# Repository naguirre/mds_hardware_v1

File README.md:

# mds-hardware

KiCad sources and fabrication outputs for a small network audio player board built around an Allwinner F1C200s SoC, an ESP32-C3 for Wi-Fi, NAND flash storage, an EA3036 power management IC, and an audio DAC daughter board.

The repository contains two KiCad projects:
- [network_player/](network_player/) — the main board
- [dac/](dac/) — the audio DAC daughter board

## Versions

| Version | Date       | Status                                         | Schematic | PCB | Gerbers |
|---------|------------|------------------------------------------------|-----------|-----|---------|
| v1      | 2024-01-15 | Sent to JLCPCB, had routing issues             | [PDF](docs/v1/schematic.pdf) | [PDF](docs/v1/pcb.pdf) | [ZIP](docs/v1/gerbers.zip) |
| v1.1    | 2024-06-02 | Sent to JLCPCB, fixes routing issues of v1     | [PDF](docs/v1.1/schematic.pdf) | [PDF](docs/v1.1/pcb.pdf) | [ZIP](docs/v1.1/gerbers.zip) |
| v2      | 2024-06-01 | Full redesign, never produced                  | [PDF](docs/v2/schematic.pdf) | [PDF](docs/v2/pcb.pdf) | [ZIP](docs/v2/gerbers.zip) |

Each version lives on its own branch: [`users/nico/v1`](../../tree/users/nico/v1), [`users/nico/v1.1`](../../tree/users/nico/v1.1), [`users/nico/v2`](../../tree/users/nico/v2). The `v1_jlcpcb` tag points to the JLCPCB return files for v1.

## Latest produced version: v1.1

v1.1 is the version that was actually fabricated and assembled by JLCPCB. Compared to v1, it brings the following changes (see commit [b7ff0fe](../../commit/b7ff0fe)):

- Removed the discrete transistors used for ESP32 boot/reset, driven directly from F1C200s GPIOs instead
- EA3036 enable pin tied to 3.3 V
- Added a RST button that pulls the MISO line to ground to disable booting from flash
- ESP32 moved to SPI1; SPI0 is now shared between the NAND flash and the RPi connector

### Schematic

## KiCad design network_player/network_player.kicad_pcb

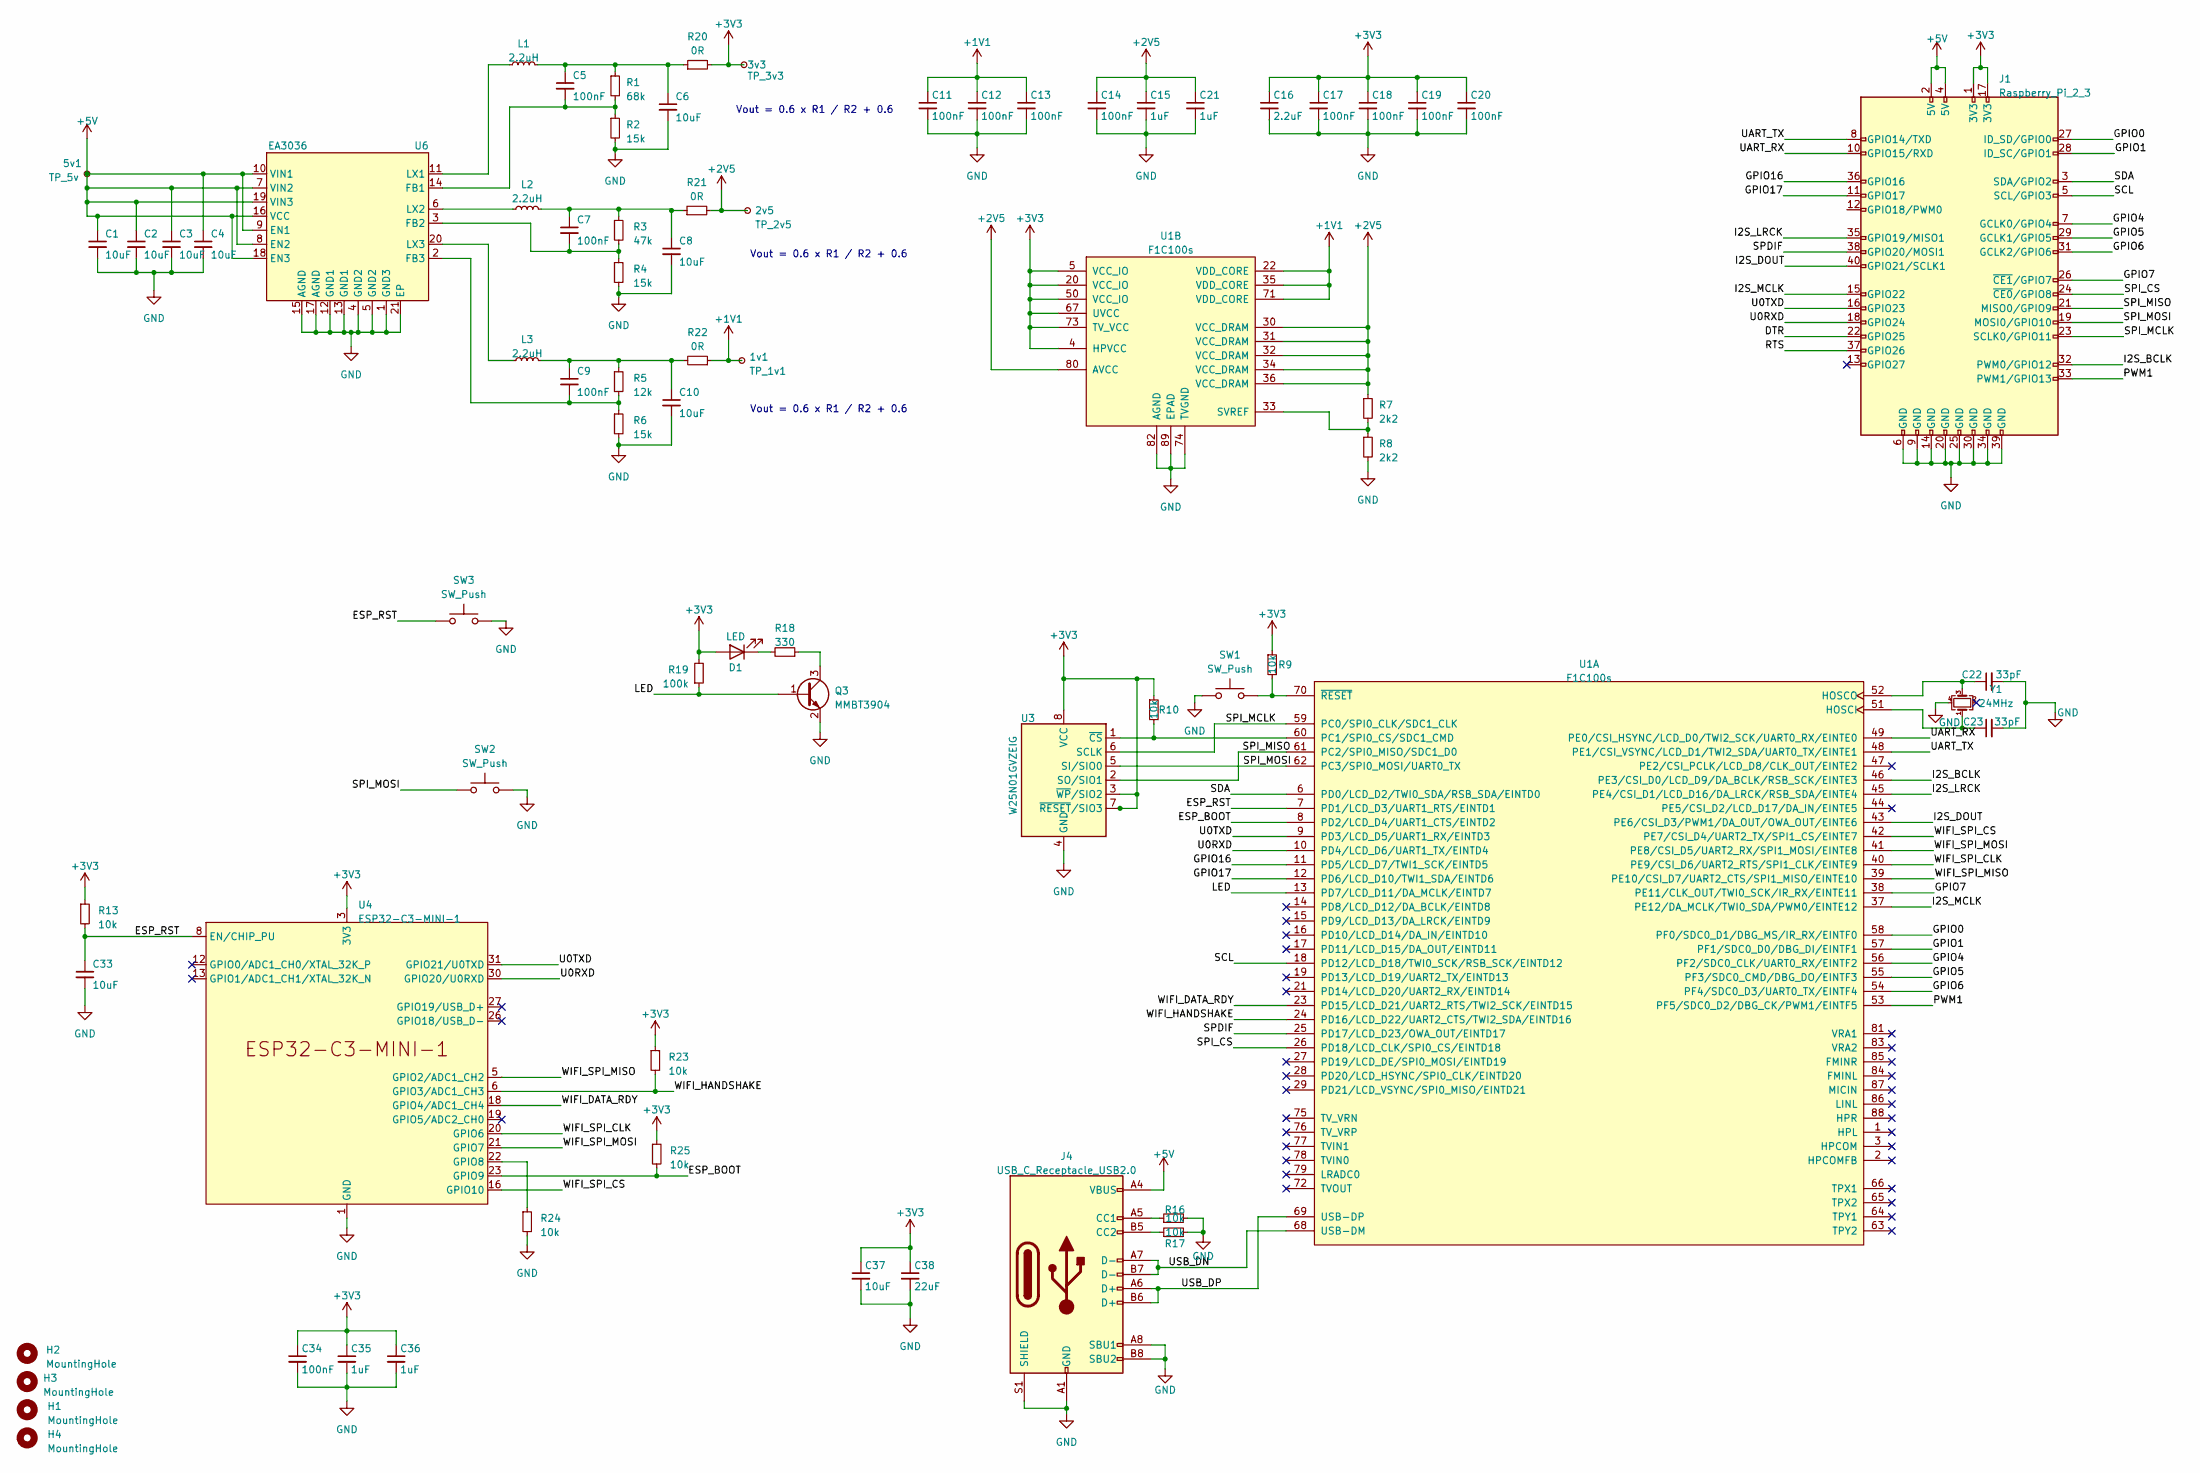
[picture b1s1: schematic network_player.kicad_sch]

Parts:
1v1: TP_1v1; TestPoint_Pad_D1.0mm
2v5: TP_2v5; TestPoint_Pad_D1.0mm
3v3: TP_3v3; TestPoint_Pad_D1.0mm
5v1: TP_5v; TestPoint_Pad_D1.0mm
C1, C2, C3, C4, C6, C8, C10, C33, C37: 10uF; C_0402_1005Metric; LCSC C15525
C5, C7, C9, C11, C12, C13, C14, C17, C18, C19, C20, C34: 100nF; C_0402_1005Metric; LCSC C307331
C15, C21, C35, C36: 1uF; C_0402_1005Metric; LCSC C52923
C16: 2.2uF; C_0402_1005Metric; LCSC C12530
C22, C23: 33pF; C_0402_1005Metric; LCSC C1562
C38: 22uF; C_0805_2012Metric; LCSC C59461
D1: LED; LED_0603_1608Metric; LCSC C2290
H1, H2, H3, H4: MountingHole; MountingHole_2.7mm_M2.5
J1: Raspberry_Pi_2_3; PinHeader_2x20_P2.54mm_Vertical
J4: USB_C_Receptacle_USB2.0; USB_C_Receptacle_GT-USB-7010; LCSC C963370
L1, L2, L3: 2.2uH; L_0805_2012Metric; LCSC C1043
Q3: MMBT3904; SOT-23; LCSC C20526
R1: 68k; R_0402_1005Metric; LCSC C36871
R2, R4, R6: 15k; R_0402_1005Metric; LCSC C25756
R3: 47k; R_0402_1005Metric; LCSC C25792
R5: 12k; R_0402_1005Metric; LCSC C25752
R7, R8: 2k2; R_0402_1005Metric; LCSC C25879
R9, R10, R13, R16, R17, R23, R24, R25: 10k; R_0402_1005Metric; LCSC C25744
R18: 330; R_0402_1005Metric; LCSC C25104
R19: 100k; R_0402_1005Metric; LCSC C25741
R20, R21, R22: 0R; R_0402_1005Metric; LCSC C17168
SW1, SW2, SW3: SW_Push; SW_Push_1P1T_XKB_TS-1187A; LCSC C318884
U1: F1C100s; QFN-88_EP_10x10_Pitch0.4mm; LCSC C2879851
U3: W25N01GVZEIG; WSON-8-1EP_8x6mm_P1.27mm_EP3.4x4.3mm; LCSC C88868
U4: ESP32-C3-MINI-1; LCSC C2838502
U6: EA3036; QFN-20-1EP_3x3mm_P0.4mm_EP1.65x1.65mm; LCSC C570857
Y1: 24MHz; Crystal_SMD_SeikoEpson_TSX3225-4Pin_3.2x2.5mm; LCSC C15643

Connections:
+1V1: 1v1.1, C11.1, C12.1, C13.1, R22.1, U1.22 (VDD_CORE), U1.35 (VDD_CORE), U1.71 (VDD_CORE)
+2V5: 2v5.1, C14.1, C15.1, C21.1, R7.1, R21.2, U1.30 (VCC_DRAM), U1.31 (VCC_DRAM), U1.32 (VCC_DRAM), U1.34 (VCC_DRAM), U1.36 (VCC_DRAM), U1.80 (AVCC)
+3V3: 3v3.1, C16.1, C17.1, C18.1, C19.1, C20.1, C34.1, C35.1, C36.1, C37.1, C38.1, D1.2 (A), J1.1 (3V3), J1.17 (3V3), R9.1, R10.1, R13.1, R19.2, R20.2, R23.1, R25.1, U1.4 (HPVCC), U1.5 (VCC_IO), U1.20 (VCC_IO), U1.50 (VCC_IO), U1.67 (UVCC), U1.73 (TV_VCC), U3.3 (~WP/SIO2), U3.7 (~RESET/SIO3), U3.8 (VCC), U4.3 (3V3)
+5V: 5v1.1, C1.1, C2.1, C3.1, C4.1, J1.2 (5V), J1.4 (5V), J4.A4 (VBUS), J4.A9 (VBUS), J4.B4 (VBUS), J4.B9 (VBUS), U6.7 (VIN2), U6.8 (EN2), U6.9 (EN1), U6.10 (VIN1), U6.16 (VCC), U6.18 (EN3), U6.19 (VIN3)
/DTR: J1.22 (GPIO25)
/ESP_BOOT: R25.2, U1.8 (PD2/LCD_D4/UART1_CTS/EINTD2), U4.23 (GPIO9)
/ESP_RST: C33.1, R13.2, SW3.1, U1.7 (PD1/LCD_D3/UART1_RTS/EINTD1), U4.8 (EN/CHIP_PU)
/GPIO0: J1.27 (ID_SD/GPIO0), U1.58 (PF0/SDC0_D1/DBG_MS/IR_RX/EINTF0)
/GPIO1: J1.28 (ID_SC/GPIO1), U1.57 (PF1/SDC0_D0/DBG_DI/EINTF1)
/GPIO4: J1.7 (GCLK0/GPIO4), U1.56 (PF2/SDC0_CLK/UART0_RX/EINTF2)
/GPIO5: J1.29 (GCLK1/GPIO5), U1.55 (PF3/SDC0_CMD/DBG_DO/EINTF3)
/GPIO6: J1.31 (GCLK2/GPIO6), U1.54 (PF4/SDC0_D3/UART0_TX/EINTF4)
/GPIO7: J1.26 (~CE1/GPIO7), U1.38 (PE11/CLK_OUT/TWI0_SCK/IR_RX/EINTE11)
/GPIO16: J1.36 (GPIO16), U1.11 (PD5/LCD_D7/TWI1_SCK/EINTD5)
/GPIO17: J1.11 (GPIO17), U1.12 (PD6/LCD_D10/TWI1_SDA/EINTD6)
/I2S_BCLK: J1.32 (PWM0/GPIO12), U1.46 (PE3/CSI_D0/LCD_D9/DA_BCLK/RSB_SCK/EINTE3)
/I2S_DOUT: J1.40 (GPIO21/SCLK1), U1.43 (PE6/CSI_D3/PWM1/DA_OUT/OWA_OUT/EINTE6)
/I2S_LRCK: J1.35 (GPIO19/MISO1), U1.45 (PE4/CSI_D1/LCD_D16/DA_LRCK/RSB_SDA/EINT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)
/I2S_MCLK: J1.15 (GPIO22), U1.37 (PE12/DA_MCLK/TWI0_SDA/PWM0/EINTE12)
/LED: Q3.1 (B), R19.1, U1.13 (PD7/LCD_D11/DA_MCLK/EINTD7)
/PWM1: J1.33 (PWM1/GPIO13), U1.53 (PF5/SDC0_D2/DBG_CK/PWM1/EINTF5)
/RTS: J1.37 (GPIO26)
/SCL: J1.5 (SCL/GPIO3), U1.18 (PD12/LCD_D18/TWI0_SCK/RSB_SCK/EINTD12)
/SDA: J1.3 (SDA/GPIO2), U1.6 (PD0/LCD_D2/TWI0_SDA/RSB_SDA/EINTD0)
/SPDIF: J1.38 (GPIO20/MOSI1), U1.25 (PD17/LCD_D23/OWA_OUT/EINTD17)
/SPI_CS: J1.24 (~CE0/GPIO8), U1.26 (PD18/LCD_CLK/SPI0_CS/EINTD18)
/SPI_MCLK: J1.23 (SCLK0/GPIO11), U1.59 (PC0/SPI0_CLK/SDC1_CLK), U3.6 (SCLK)
/SPI_MISO: J1.21 (MISO0/GPIO9), U1.61 (PC2/SPI0_MISO/SDC1_D0), U3.2 (SO/SIO1)
/SPI_MOSI: J1.19 (MOSI0/GPIO10), SW2.1, U1.62 (PC3/SPI0_MOSI/UART0_TX), U3.5 (SI/SIO0)
/U0RXD: J1.18 (GPIO24), U1.10 (PD4/LCD_D6/UART1_TX/EINTD4), U4.30 (GPIO20/U0RXD)
/U0TXD: J1.16 (GPIO23), U1.9 (PD3/LCD_D5/UART1_RX/EINTD3), U4.31 (GPIO21/U0TXD)
/UART_RX: J1.10 (GPIO15/RXD), U1.49 (PE0/CSI_HSYNC/LCD_D0/TWI2_SCK/UART0_RX/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)
/UART_TX: J1.8 (GPIO14/TXD), U1.48 (PE1/CSI_VSYNC/LCD_D1/TWI2_SDA/UART0_TX/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)
/USB_DN: J4.A7 (D-), J4.B7 (D-), U1.68 (USB-DM)
/USB_DP: J4.A6 (D+), J4.B6 (D+), U1.69 (USB-DP)
/WIFI_DATA_RDY: U1.23 (PD15/LCD_D21/UART2_RTS/TWI2_SCK/EINTD15), U4.18 (GPIO4/ADC1_CH4)
/WIFI_HANDSHAKE: R23.2, U1.24 (PD16/LCD_D22/UART2_CTS/TWI2_SDA/EINTD16), U4.6 (GPIO3/ADC1_CH3)
/WIFI_SPI_CLK: U1.40 (PE9/CSI_D6/UART2_RTS/SPI1_CLK/EINTE9), U4.20 (GPIO6)
/WIFI_SPI_CS: U1.42 (PE7/CSI_D4/UART2_TX/SPI1_CS/EINTE7), U4.16 (GPIO10)
/WIFI_SPI_MISO: U1.39 (PE10/CSI_D7/UART2_CTS/SPI1_MISO/EINTE10), U4.5 (GPIO2/ADC1_CH2)
/WIFI_SPI_MOSI: U1.41 (PE8/CSI_D5/UART2_RX/SPI1_MOSI/EINTE8), U4.21 (GPIO7)
GND: C1.2, C2.2, C3.2, C4.2, C6.2, C8.2, C10.2, C11.2, C12.2, C13.2, C14.2, C15.2, C16.2, C17.2, C18.2, C19.2, C20.2, C21.2, C22.2, C23.2, C33.2, C34.2, C35.2, C36.2, C37.2, C38.2, J1.6 (GND), J1.9 (GND), J1.14 (GND), J1.20 (GND), J1.25 (GND), J1.30 (GND), J1.34 (GND), J1.39 (GND), J4.A1 (GND), J4.A8 (SBU1), J4.A12 (GND), J4.B1 (GND), J4.B8 (SBU2), J4.B12 (GND), J4.S1 (SHIELD), Q3.2 (E), R2.2, R4.2, R6.2, R8.2, R16.2, R17.2, R24.2, SW1.1, SW2.2, SW3.2, U1.74 (TVGND), U1.82 (AGND), U1.89 (EPAD), U3.4 (GND), U3.9 (GND), U4.1 (GND), U4.2 (GND), U4.11 (GND), U4.14 (GND), U4.36 (GND), U4.37 (GND), U4.38 (GND), U4.39 (GND), U4.40 (GND), U4.41 (GND), U4.42 (GND), U4.43 (GND), U4.44 (GND), U4.45 (GND), U4.46 (GND), U4.47 (GND), U4.48 (GND), U4.49 (GND), U4.50 (GND), U4.51 (GND), U4.52 (GND), U4.53 (GND), U6.1 (GND3), U6.4 (GND2), U6.5 (GND2), U6.12 (GND1), U6.13 (GND1), U6.15 (AGND), U6.17 (AGND), U6.21 (EP), Y1.4
unnamed: C5.1, C6.1, L1.2, R1.1, R20.1
unnamed: C7.1, C8.1, L2.2, R3.1, R21.1
unnamed: C9.1, C10.1, L3.2, R5.1, R22.2
unnamed: D1.1 (K), R18.2
unnamed: J4.A5 (CC1), R16.1
unnamed: J4.B5 (CC2), R17.1
unnamed: Q3.3 (C), R18.1
unnamed: C23.1, U1.51 (HOSCI), Y1.1
unnamed: C22.1, U1.52 (HOSCO), Y1.3
unnamed: R10.2, U1.60 (PC1/SPI0_CS/SDC1_CMD), U3.1 (~CS)
unnamed: R9.2, SW1.2, U1.70 (~RESET)
unnamed: R7.2, R8.1, U1.33 (SVREF)
unnamed: R24.1, U4.22 (GPIO8)
unnamed: C5.2, R1.2, R2.1, U6.14 (FB1)
unnamed: C7.2, R3.2, R4.1, U6.3 (FB2)
unnamed: C9.2, R5.2, R6.1, U6.2 (FB3)
unnamed: L1.1, U6.11 (LX1)
unnamed: L2.1, U6.6 (LX2)
unnamed: L3.1, U6.20 (LX3)

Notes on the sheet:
Vout = 0.6 x R1 / R2 + 0.6

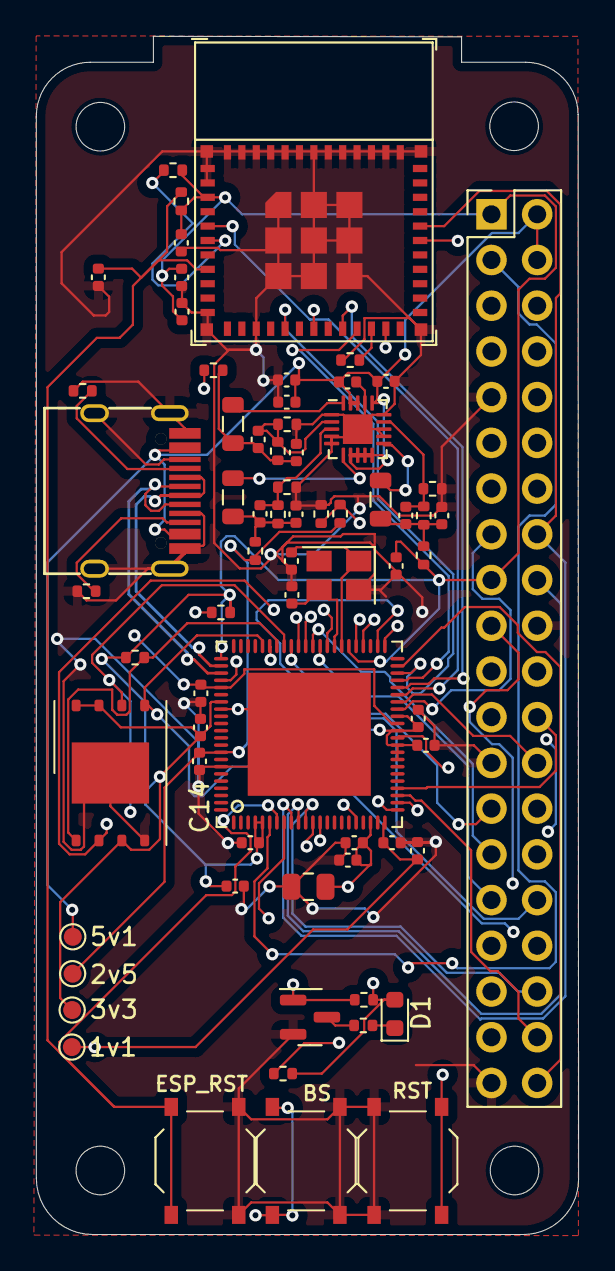
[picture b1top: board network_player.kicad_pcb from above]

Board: 4 copper layers, 30.1 x 66.6 mm, 73 parts (0 on the bottom side), 59 nets.

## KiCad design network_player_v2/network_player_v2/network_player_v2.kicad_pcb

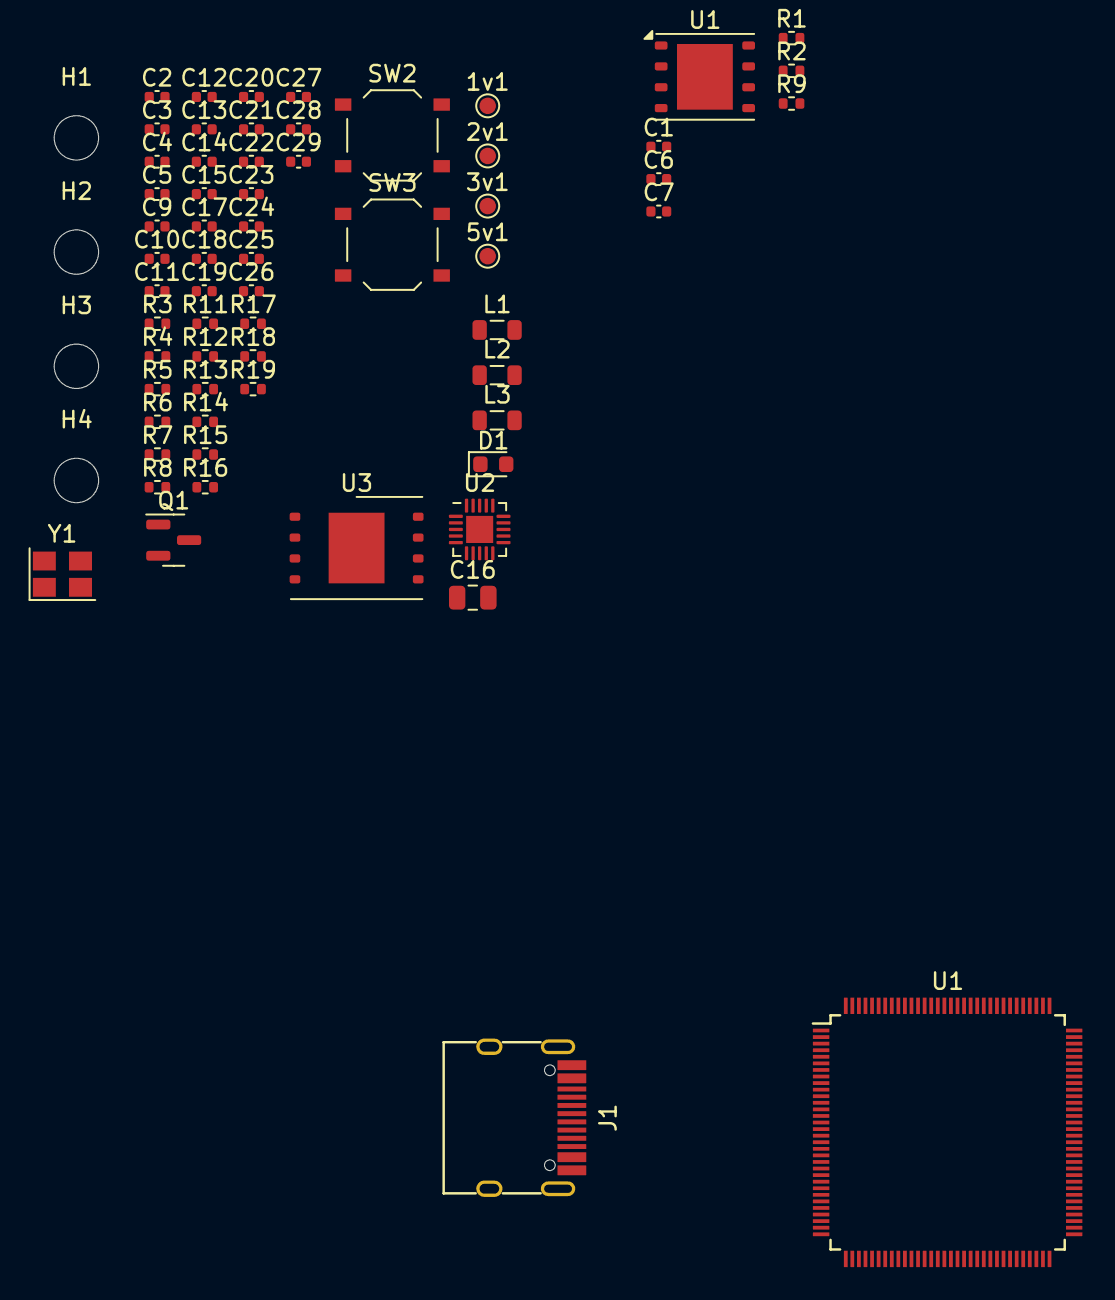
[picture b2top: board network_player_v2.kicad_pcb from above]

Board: 2 copper layers, 67 parts (0 on the bottom side), 29 nets, no tracks yet.

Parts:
1v1: TP_1v1; TestPoint_Pad_D1.0mm
2v1: TP_2v5; TestPoint_Pad_D1.0mm
3v1: TP_3v3; TestPoint_Pad_D1.0mm
5v1: TP_5v; TestPoint_Pad_D1.0mm
C1, C6, C28, C29: 33pF; C_0402_1005Metric
C2, C3, C4, C5, C12, C13, C14, C15: 10uF; C_0402_1005Metric
C7, C9, C10, C11, C17, C18, C19, C20, C24, C25, C26, C27: 100nF; C_0402_1005Metric
C16: 22uF; C_0805_2012Metric
C21, C22: 1uF; C_0402_1005Metric
C23: 2.2uF; C_0402_1005Metric
D1: LED; LED_0603_1608Metric
H1, H2, H3, H4: MountingHole; MountingHole_2.7mm_M2.5
J1: USB_C_Receptacle_USB2.0; USB_C_Receptacle_GT-USB-7010
L1, L2, L3: 2.2uH; L_0805_2012Metric
Q1: MMBT3904; SOT-23
R1: 640K; R_0402_1005Metric
R2, R14: 100k; R_0402_1005Metric
R3: 68k; R_0402_1005Metric
R4, R6, R8: 15k; R_0402_1005Metric
R5: 47k; R_0402_1005Metric
R7: 12k; R_0402_1005Metric
R9: 150k; R_0402_1005Metric
R11, R12, R13: 0R; R_0402_1005Metric
R15: 330; R_0402_1005Metric
R16, R17, R18, R19: 10k; R_0402_1005Metric
SW2, SW3: SW_Push; SW_Push_1P1T_XKB_TS-1187A
U1: F1C100s; TQFP-128_14x14mm_P0.4mm
U1#2: MX25R3235FZNxx0; WSON-8-1EP_6x5mm_P1.27mm_EP3.4x4mm
U2: EA3036; QFN-20-1EP_3x3mm_P0.4mm_EP1.65x1.65mm
U3: W25N01GVZEIG; WSON-8-1EP_8x6mm_P1.27mm_EP3.4x4.3mm
Y1: 24MHz; Crystal_SMD_SeikoEpson_TSX3225-4Pin_3.2x2.5mm

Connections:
+1V1: 1v1.1, C17.1, C18.1, C19.1, R13.1
+2V5: 2v1.1, C20.1, C21.1, C22.1, R11.2
+3V3: 3v1.1, C15.1, C16.1, C23.1, C24.1, C25.1, C26.1, C27.1, D1.2 (A), R2.2, R12.2, R14.2, R16.1, R19.1, U1#2.3 (~WP/SIO2), U1#2.7 (~RESET/SIO3), U1#2.8 (VCC), U3.3 (~WP/SIO2), U3.7 (~RESET/SIO3), U3.8 (VCC)
+5V: 5v1.1, C2.1, C3.1, C4.1, C5.1, J1.A4 (VBUS), J1.A9 (VBUS), J1.B4 (VBUS), J1.B9 (VBUS), U2.7 (VIN2), U2.8 (EN2), U2.9 (EN1), U2.10 (VIN1), U2.16 (VCC), U2.19 (VIN3)
/LED: Q1.1 (B), R14.1
/RESET: R19.2, SW3.2
/SPI_MOSI: SW2.1, U3.5 (SI/SIO0)
GND: C1.2, C2.2, C3.2, C4.2, C5.2, C6.2, C7.2, C12.2, C13.2, C14.2, C15.2, C16.2, C17.2, C18.2, C19.2, C20.2, C21.2, C22.2, C23.2, C24.2, C25.2, C26.2, C27.2, C28.2, C29.2, J1.A1 (GND), J1.A8 (SBU1), J1.A12 (GND), J1.B1 (GND), J1.B8 (SBU2), J1.B12 (GND), J1.S1 (SHIELD), Q1.2 (E), R4.2, R6.2, R8.2, R9.2, R17.2, R18.2, SW2.2, SW3.1, U1#2.4 (GND), U1#2.9 (GND), U2.1 (GND3), U2.4 (GND2), U2.5 (GND2), U2.12 (GND1), U2.13 (GND1), U2.15 (AGND), U2.17 (AGND), U2.21 (EP), U3.4 (GND), U3.9 (GND), Y1.4
unnamed: C10.1, C13.1, L2.2, R5.1, R11.1
unnamed: C11.1, C14.1, L3.2, R7.1, R13.2
unnamed: C9.1, C12.1, L1.2, R3.1, R12.1
unnamed: D1.1 (K), R15.2
unnamed: J1.A5 (CC1), R17.1
unnamed: J1.B5 (CC2), R18.1
unnamed: J1.A7 (D-), J1.B7 (D-)
unnamed: Q1.3 (C), R15.1
unnamed: R16.2, U1#2.1 (~CS)
unnamed: C7.1, R2.1, R9.1, U2.18 (EN3)
unnamed: C9.2, R3.2, R4.1, U2.14 (FB1)
unnamed: C10.2, R5.2, R6.1, U2.3 (FB2)
unnamed: C11.2, R7.2, R8.1, U2.2 (FB3)
unnamed: L1.1, U2.11 (LX1)
unnamed: L2.1, U2.6 (LX2)
unnamed: L3.1, U2.20 (LX3)
unnamed: C28.1, Y1.3
unnamed: C29.1, Y1.1
unnamed: J1.A6 (D+), J1.B6 (D+)
unnamed: C1.1, R1.1
unnamed: C6.1, R1.2

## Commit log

2024-01-15 This version sent to JLCPCB on 15 January 2024
2024-01-15 Change footprint of EA3036 and generate gerbers + drill files
2024-01-15 Fully update gerbers before sending again to jlcpcb, also add silkscreen with copyright
2024-01-15 add zip upload to website
2024-01-25 Upload file coming fron JLCPCB
2024-07-07 first corrections
2024-07-07 Modifications for v1.1
    - Remove transistors for ESP32 boot/reset and use GPIO from f1c200s
    - Connect EA3036 enable to 3.3v
    - Add RST button to tie MISO line to ground to disable booting from flash
    - Use SPI1 for ESP32 and connect SPI0 to Nand Flash and RPI connector
2024-07-07 Add bon
2024-07-07 Add pos file
2024-07-07 Add missing files
2024-07-07 Add pdf for schematics
2024-07-07 Add cern licence
2024-10-06 Push frist v2 ideas
2024-10-18 architecture.drawio
2024-10-18 architecure.drawio
2024-11-18 recover for v1.1
2024-12-23 Add pdf and png files
2026-05-10 Rewrite README with version history and add docs/ artifacts
2026-05-10 Remove accidentally committed .DS_Store
2026-05-10 Add .gitignore for macOS, Claude, tmp/ and KiCad caches
2026-05-10 Fix README links to GitHub refs and regenerate v2 artifacts from network_player_v2 (T113-s3)

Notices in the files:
network_player/network_player.kicad_pcb:
(c) 2024
